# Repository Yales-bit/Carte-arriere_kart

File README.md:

## Aperçu du projet

[Voir le Schéma du circuit (PDF)](https://raw.githubusercontent.com/Yales-bit/Carte-arriere_kart/assets/images/Schema/schema_complet.pdf)

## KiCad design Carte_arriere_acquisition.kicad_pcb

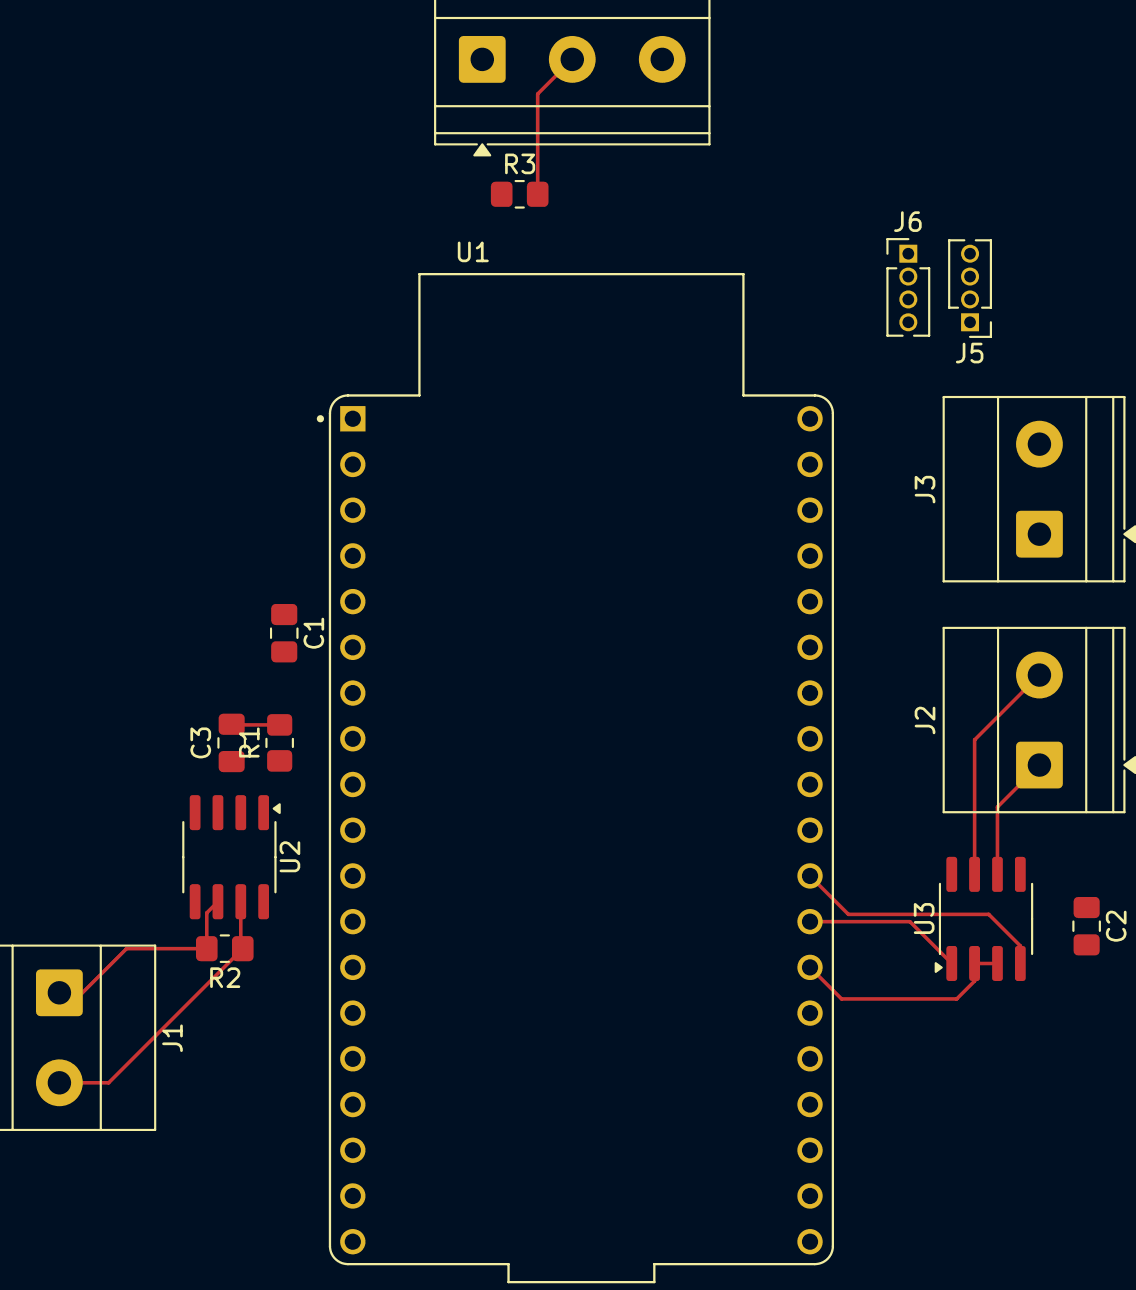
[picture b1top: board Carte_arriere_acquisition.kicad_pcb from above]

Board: 2 copper layers, 15 parts (0 on the bottom side), 18 nets.

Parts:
C1, C2, C3: 100nF; C_0805_2012Metric_Pad1.18x1.45mm_HandSolder
J1: Screw_Terminal_01x02; TerminalBlock_Phoenix_MKDS-1,5-2_1x02_P5.00mm_Horizontal
J2: Vers_BMS; TerminalBlock_Phoenix_MKDS-1,5-2_1x02_P5.00mm_Horizontal
J3: Vers_Thermistor; TerminalBlock_Phoenix_MKDS-1,5-2_1x02_P5.00mm_Horizontal
J4: Vers_Capteur_Hall; TerminalBlock_Phoenix_MKDS-1,5-3_1x03_P5.00mm_Horizontal
J5, J6: Conn_01x04_Pin; PinHeader_1x04_P1.27mm_Vertical
R1: 1k; R_0805_2012Metric_Pad1.20x1.40mm_HandSolder
R2: 120; R_0805_2012Metric_Pad1.20x1.40mm_HandSolder
R3: 10k; R_0805_2012Metric_Pad1.20x1.40mm_HandSolder
U1: ESP32-DEVKITC-32E; MODULE_ESP32-DEVKITC-32E
U2: SN65HVD230; SOIC-8_3.9x4.9mm_P1.27mm
U3: MAX3485; SOIC-8_3.9x4.9mm_P1.27mm

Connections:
+3.3V: C1.1, C2.1, C3.1, J3.1, J4.1, J6.3, R3.1, U1.J2_1 (3V3), U1.J2_5 (IO34), U2.3 (VCC), U3.8 (VCC)
/BMS RX: U1.J3_12 (IO16), U3.1 (RO)
/BMS TX: U1.J3_11 (IO17), U3.4 (DI)
/BMS_Direction: U1.J3_13 (IO4), U3.2 (~RE), U3.3 (DE)
/CAN_RX: U1.J2_11 (IO27), U2.4 (R)
/CAN_TX: U1.J2_10 (IO26), U2.1 (D)
/GPIO5: J5.2, U1.J3_10 (IO5)
/GPIO18: J5.3, U1.J3_9 (IO18)
/GPIO19: J5.4, U1.J3_8 (IO19)
/Hall: J4.2, R3.2, U1.J2_6 (IO35)
/SCL: J6.2, U1.J3_6 (IO21)
/SDA: J6.1, U1.J3_3 (IO22)
GND: C1.2, C2.2, C3.2, J3.2, J4.3, J6.4, R1.2, U1.J3_1 (GND_J3_1), U2.2 (GND), U3.5 (GND)
unnamed: J1.1, R2.2, U2.6 (CANL)
unnamed: J1.2, R2.1, U2.7 (CANH)
unnamed: J2.1, U3.6 (A)
unnamed: J2.2, U3.7 (B)
unnamed: R1.1, U2.8 (Rs)

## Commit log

2026-04-01 Initial commit : Schéma et PCB de base
2026-04-01 ajout des libraries
2026-04-01 Add .gitignore for backup and output files
2026-04-01 Add configuration for Kibot outputs
2026-04-01 Ajout workflow generation jpg
2026-04-01 Add project overview and images to README
2026-04-01 modif workflow
2026-04-01 test
2026-04-01 Add PDF link for circuit schematic in README
    Added a link to view the circuit schematic in PDF format.
2026-04-01 modif wf
2026-04-01 Update output directories to include parent Export
2026-04-01 Mise à jour automatique des visuels (KiCad 9)
2026-04-01 modif
2026-04-01 Update circuit diagram link in README
2026-04-01 Update .gitignore to include additional backup files
2026-04-01 Modif PCB
2026-04-01 Changement capteur temp
2026-04-01 ajout IMU
2026-04-01 mise a jour
